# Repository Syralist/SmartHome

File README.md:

# SmartHome
Meine Smarthome Projekte

## Floorplan Credits
Door Symbol by [Santiago Arias](https://thenounproject.com/term/door/736133/)

Window Symbol by [Santiago Arias](https://thenounproject.com/term/door/736131/) 

Database Symbol by [Arthur Shlain](https://thenounproject.com/term/door/87613/) 

Display Symbol by [Arthur Shlain](https://thenounproject.com/term/door/86221/)

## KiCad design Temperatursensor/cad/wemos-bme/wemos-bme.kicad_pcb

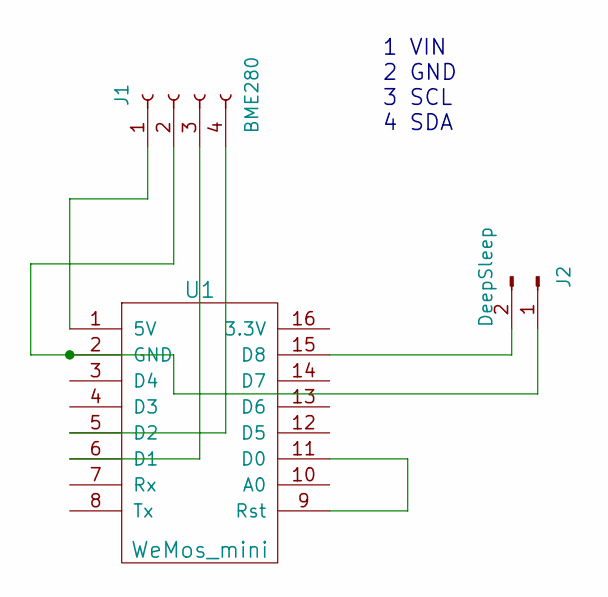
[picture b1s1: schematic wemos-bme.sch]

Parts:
J1: BME280; Pin_Header_Straight_1x04_Pitch2.54mm
J2: DeepSleep; Pin_Header_Straight_1x02_Pitch2.54mm
U1: WeMos_mini; D1_mini_board

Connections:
unnamed: J1.1, U1.1 (5V)
unnamed: J1.2, J2.1, U1.2 (GND)
unnamed: J1.3, U1.6 (D1)
unnamed: J1.4, U1.5 (D2)
unnamed: J2.2, U1.15 (D8)
unnamed: U1.9 (Rst), U1.11 (D0)

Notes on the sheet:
1 VIN 2 GND 3 SCL 4 SDA

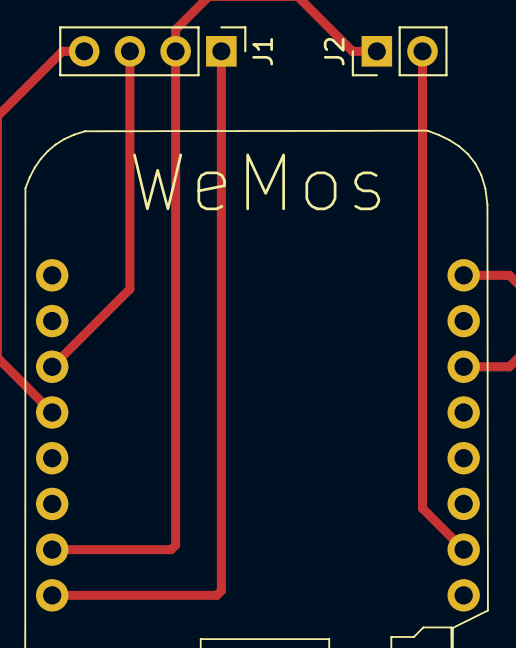
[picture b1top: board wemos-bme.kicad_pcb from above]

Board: 2 copper layers, 3 parts (0 on the bottom side), 6 nets.

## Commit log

2018-04-19 Wemos mit BME280 und MQTT
2018-04-20 PCB für Temperatursensor
2018-04-21 HomeAssistant Konfiguration hinzugefügt
2018-04-21 Default Topic korrigiert
2018-04-24 Duckdns und Owntracks aktiviert.
2018-04-24 Telegram Bot hinzugefügt.
2018-04-25 Waschmaschinensensor mit MQTT hinzugefügt.
2018-04-30 Sensor in Steffis Zimmer hinzugefügt
2018-04-30 HDMI CEC hinzugefügt und eine Scene erstellt.
2018-05-06 Sonoff Switch hinzugefügt
2018-05-08 Google Kalender integriert.
2018-05-12 gitignore erweitert
2018-05-12 Sensor für Thomas Zimmer hinzugefügt
2018-05-16 Synology als Wake-on-Lan Switch hinzugefügt.
2018-05-19 OpenMQTTGateway als submodule hinzugefügt
2018-06-04 USV eingebunden. Drucker-Gruppe eingerichtet.
2018-06-06 Benachrichtigung bei Stromausfall und InfluxDB hinzugefügt.
2018-06-17 Floorplan hinzugefügt
2018-06-18 Gehäuse entworfen
2018-06-18 Gehäuse korrigiert
2018-06-18 Button am Temperatursensor hinzugefügt. Schickt MQTT Message bei Klick und bei Halten. Automatisierung für Sonoff Rechner.
2018-06-23 Langer Tastendruck fährt jetzt die ganze Gruppe herunter.
2018-07-03 TasmoAdmin hinzugefügt
2018-07-09 Sonoff Pow für die Waschmaschine konfiguriert.
2018-07-12 Fernseher als MediaPlayer eingerichtet.
2018-07-13 Notification: Wäsche fertig. ISS sensor. Systeminformation.
2018-07-13 Einschaltverzögerung für Waschmaschine läuft.
2018-07-19 Cloud aktiviert und Alexa konfiguriert. Scene Film gucken vereinfacht.
2018-07-25 Eufy Glühbirne hinzugefügt.
2018-08-12 Lovelace
2018-09-08 Bewegungsmelder mit MQTT
2018-09-08 automatisches Backup auf Dropbox
2018-09-08 OpenMQTTGateway entfernt
2018-09-14 interaktive Statusabfrage über Telegram-Bot.
2018-10-02 influxdb und cloud entfernt. devicetracker auf nmap umgestellt.
2018-10-04 Fensterkontakte eingebunden. Neues Handy.
2018-10-06 Batteriezustände der Fensterkontakte. Neue Infos für Jarvis.
2018-10-06 Temperatursensor senden nur noch einmal pro Sekunde. Button kann per #define eingeschaltet werden.
2018-10-06 Gehäuse für Bewegungsmelder
2018-10-07 Wake on Lan und Remote Shutdown für den Rechner.
2018-10-31 LED Lampe mit MQTT
2018-11-01 LED Stripe with McLightning
2018-11-07 Anpassungen an neue Mosquitto Version.
2018-11-07 Timeout verlängert. Neue Mosquitto Authentification dauert länger.
2018-11-18 Lixie Clock als Uhr hinzugefügt
2018-11-24 ISS Einträge entfernt. Batterystatus Haustürsensor zugefügt.
2018-12-02 Homematic und Tuya aktiviert.
2019-01-22 Main change: Homematic on extra raspi.
2019-02-28 Homematic Fensterkontakt und Fritzbox Netmonitor hinzugefügt.
2019-03-10 erster Test des Statusdisplays mit Bitmaps.
2019-03-16 Bitmap-Funktionen in eigene Datei verschoben. Weitere Tests mit Rahmen.
2019-04-07 ViCare Component, Temperatursensor in der LixieClock.
2019-04-28 neues Dropbox-Addon, McLighting angepasst, NodeRed Flows hinzugefügt vor dem Update auf 0.92.1
2019-08-04 keypad code hinzugefügt
2019-08-14 Diverse Anpassungen.
2020-02-07 aktuelle Konfiguration nachgezogen
2020-04-01 Konfiguration aufgeteilt
2021-01-15 Konfiguration aktualisiert.
